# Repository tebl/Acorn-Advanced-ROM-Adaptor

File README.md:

# Acorn Advanced ROM Adaptor

Recently picked up something called an Advanced ROM MKII Adaptor, a 16K sideways ROM- RAM Adaptor for The Acorn Electron by Advanced Computer Products. The one I have looks like the one below, unfortunately it was had no sockets so both all the ROMs were soldered in and the jumpers used to select the type of chips installed (8K SRAM, 8K ROM or 16K ROM) were nowhere to be seen so not the most exciting piece of kit in my collection. So I decided to recreate the board instead of tearing it down and hacking it to pieces.

The original release of the product had a MKI which only sported a single EPROM, the MKII as already described has the capacity for two chips with the aid of a small piece of added logic. I started by tracing out where every connection went on the MKII, adding up the details into a [schematic](https://github.com/tebl/Acorn-Advanced-ROM-Adaptor/raw/master/MK2%20Original/export/MK2%20Original.pdf) that can be found as part of the project found in*MK2 Original*. I've included them for any that would like to have that kind of information available when attempting to repair a similar cartridge.

Finally I wanted one that I could mess around with, so with the schematic in mind I started drawing out a *MKIII Redux* version of it instead. The differences here is that I've replaced the 27128/27C128, that are a pain to track down and pay for, with the plentiful 27C512 chips instead. This bumps the capacity of the cartridge from 2x16K to 8x16K, addressing is kept the same - the remaining slots are available by changing the jumper settings. 

# Versions
For added details, see following project pages:
- [MKII Original](https://github.com/tebl/Acorn-Advanced-ROM-Adaptor/tree/master/MK2%20Original)
- [MKIII Redux](https://github.com/tebl/Acorn-Advanced-ROM-Adaptor/tree/master/MK3%20Redux)

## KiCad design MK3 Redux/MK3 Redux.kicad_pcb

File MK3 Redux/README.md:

# Acorn Advanced ROM MKIII Redux

**UNTESTED**

Recently picked up something called an Advanced ROM MKII Adaptor, a 16K sideways ROM- RAM Adaptor for The Acorn Electron by Advanced Computer Products.  I've added a schematic for the MKII as part as the [MKII Original](https://github.com/tebl/Acorn-Advanced-ROM-Adaptor/tree/master/MK2%20Original), this is the *MKIII Redux* and as the name implies it is my attempt to create a cartridge that I can mess around with - without tearing down and hacking up 30 year old irreplaceable hardware.

The differences from the original design is that I've replaced the 27128/27C128, that are a pain to track down and pay for, with the plentiful 27C512. This bumps the capacity of the cartridge from 2x16K to 8x16K though addressing is kept the same, the remaining slots are available by changing the jumper settings with the computer is unplugged. I could have gone for chips that are even larger in capacity, but I wanted something that is easy enough for anyone with a soldering iron to fix up for themselves and there really aren't all that much ROM-based software available so even with the limited 8 slots you'll still fit in most of the desirable titles anyway. Smaller EPROMs such as the 27C64 or 27C256 can still be used, just keep the A14/15 lines unjumpered.

# Schematic
The supplied KiCad files should be sufficient as both a schematic and as a  starting point for ordering PCBs (basically you could just zip the contents of the export folder and upload that on a fabrication site), the schematic is also available in [PDF-format](https://github.com/tebl/Acorn-Advanced-ROM-Adaptor/raw/master/MK3%20Redux/export/MK3%20Redux.pdf) and this is what you'll need to print and work your way through this things don't work as expected after assembly.

# BOM
Most parts should be easy to get a hold of from your favourite local electronic component shop, but given that I don't have access to such shops where I live so everything was based on whatever I could get cheapest from ebay/AliExpress (free shipping, plan on usually waiting 3-4 weeks though). The list below should be everything you'll need in addition to a workable soldering iron and some 60/40 soldering tin. Other tools needed for this project is an EPROM-ereaser as well as an EPROM-programmer for the two ICs (I use MiniPro TL866 for both).

Some vendors will have the same ICs in different form factors, the ones you want will often be specified as being in the form of a DIP/PDIP package. Usually you'll want sockets for each of the ICs as well, a bag of assorted sockets should be easily available without setting you back more than a couple bucks. With the sockets in place, you don't need to dread having to remove an IC later, this leads to easier fault finding and you can even "borrow" them for other projects later! For the pin headers, you probably won't find the exact pin count so just buy the longer versions and snip off the parts you don't need.

| Reference    | Item                                  | Count |
| ------------ | ------------------------------------- | ----- |
| PCB          | Fabricate using Gerber files          |     1 |
| C1-C3        | 100nF ceramic capacitor               |     3 |
| R1           | 10k ohm resistor                      |     1 |
| U1,U2        | 27C512 DIP-28                         |     2 |
| U3           | 74HCT00 DIP-16                        |     1 |
|              | Male 2x40-pin header (break to size)  |     1 |

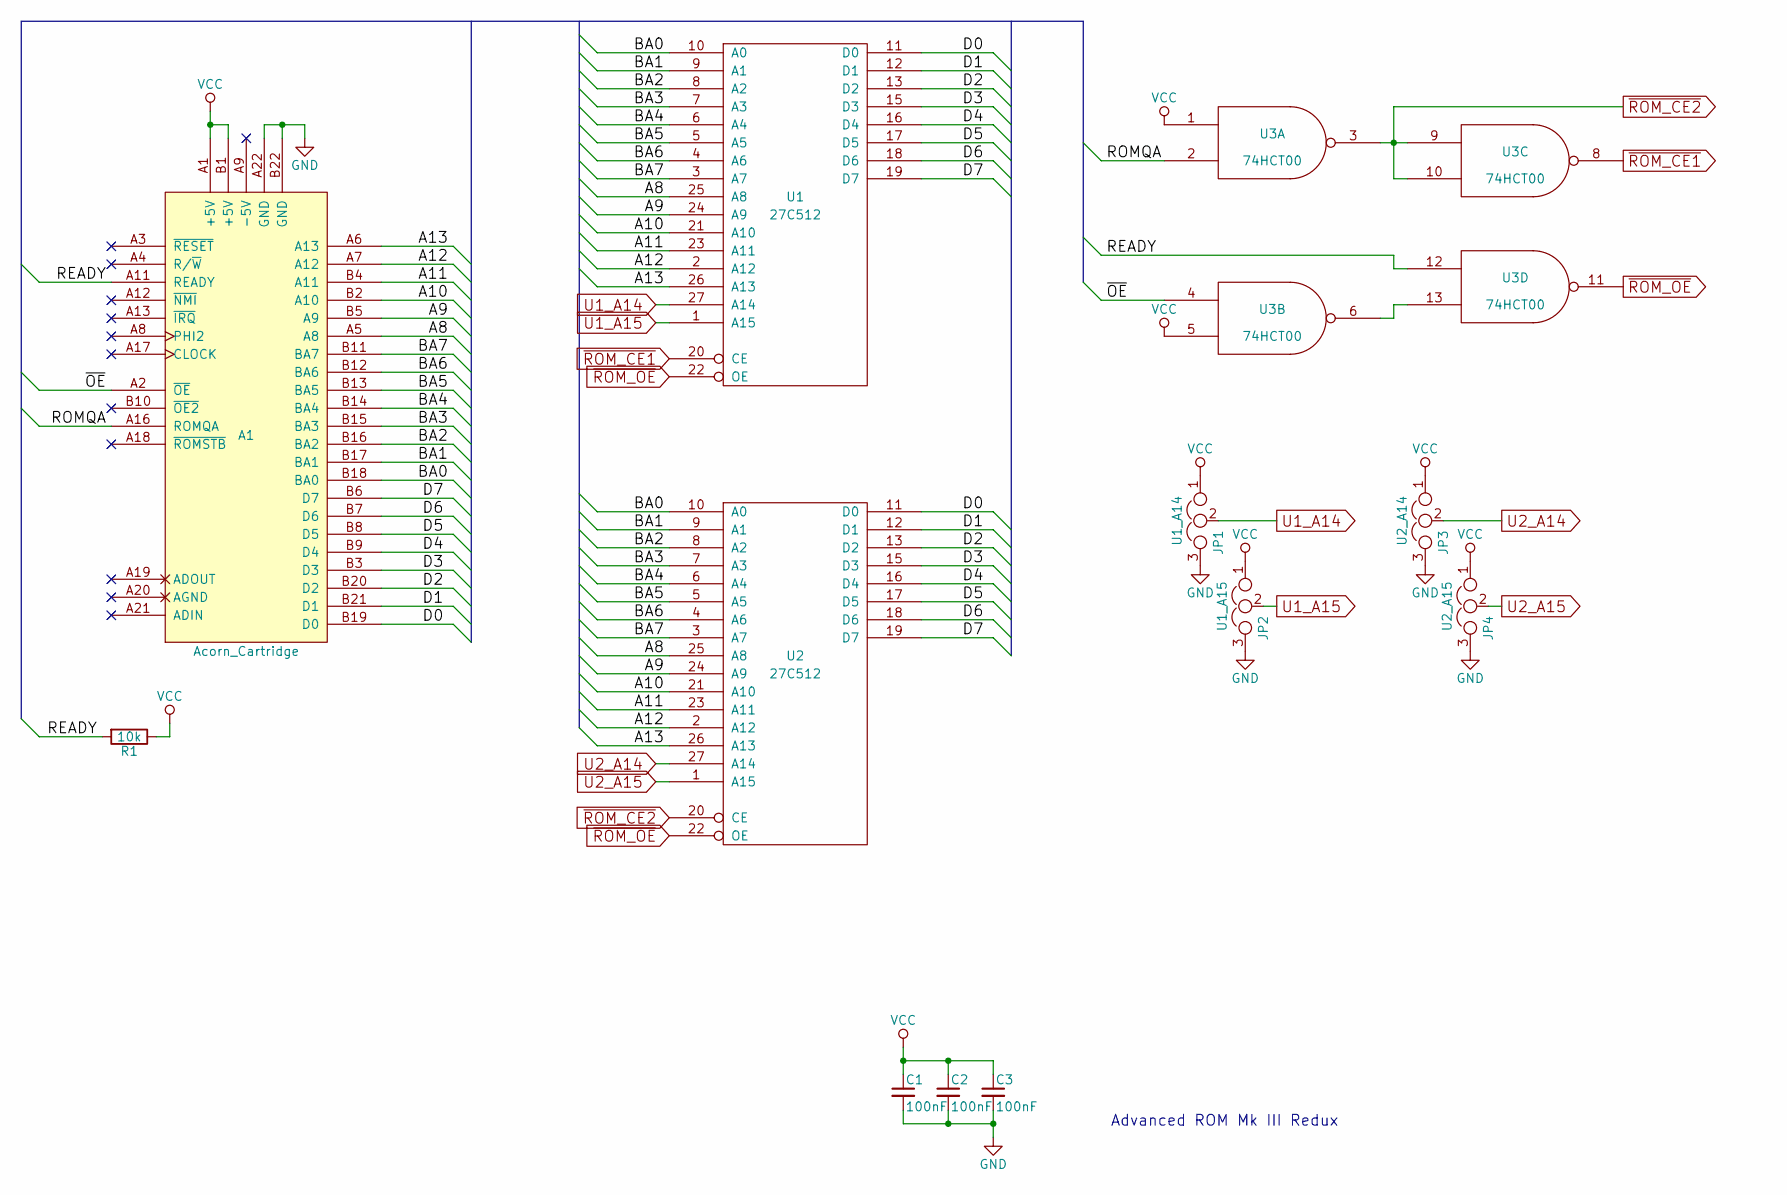
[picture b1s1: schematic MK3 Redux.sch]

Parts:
A1: Acorn_Cartridge
C1, C2, C3: 100nF; C_Disc_D4.7mm_W2.5mm_P5.00mm
JP1: U1_A14; Pin_Header_Straight_1x03_Pitch2.54mm
JP2: U1_A15; Pin_Header_Straight_1x03_Pitch2.54mm
JP3: U2_A14; Pin_Header_Straight_1x03_Pitch2.54mm
JP4: U2_A15; Pin_Header_Straight_1x03_Pitch2.54mm
R1: 10k; R_Axial_DIN0207_L6.3mm_D2.5mm_P10.16mm_Horizontal
U1, U2: 27C512; DIP-28_W15.24mm_Socket
U3: 74HCT00; DIP-14_W7.62mm_Socket

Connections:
/A8: A1.A5 (A8), U1.25 (A8), U2.25 (A8)
/A9: A1.B5 (A9), U1.24 (A9), U2.24 (A9)
/A10: A1.B2 (A10), U1.21 (A10), U2.21 (A10)
/A11: A1.B4 (A11), U1.23 (A11), U2.23 (A11)
/A12: A1.A7 (A12), U1.2 (A12), U2.2 (A12)
/A13: A1.A6 (A13), U1.26 (A13), U2.26 (A13)
/BA0: A1.B18 (BA0), U1.10 (A0), U2.10 (A0)
/BA1: A1.B17 (BA1), U1.9 (A1), U2.9 (A1)
/BA2: A1.B16 (BA2), U1.8 (A2), U2.8 (A2)
/BA3: A1.B15 (BA3), U1.7 (A3), U2.7 (A3)
/BA4: A1.B14 (BA4), U1.6 (A4), U2.6 (A4)
/BA5: A1.B13 (BA5), U1.5 (A5), U2.5 (A5)
/BA6: A1.B12 (BA6), U1.4 (A6), U2.4 (A6)
/BA7: A1.B11 (BA7), U1.3 (A7), U2.3 (A7)
/D0: A1.B19 (D0), U1.11 (D0), U2.11 (D0)
/D1: A1.B21 (D1), U1.12 (D1), U2.12 (D1)
/D2: A1.B20 (D2), U1.13 (D2), U2.13 (D2)
/D3: A1.B3 (D3), U1.15 (D3), U2.15 (D3)
/D4: A1.B9 (D4), U1.16 (D4), U2.16 (D4)
/D5: A1.B8 (D5), U1.17 (D5), U2.17 (D5)
/D6: A1.B7 (D6), U1.18 (D6), U2.18 (D6)
/D7: A1.B6 (D7), U1.19 (D7), U2.19 (D7)
/READY: A1.A11 (READY), R1.2, U3.12
/ROMQA: A1.A16 (ROMQA), U3.2
/~OE: A1.A2 (~OE), U3.4
GND: A1.A22 (GND), A1.B22 (GND), C1.2, C2.2, C3.2, JP1.3, JP2.3, JP3.3, JP4.3, U1.14 (GND), U2.14 (GND), U3.7 (GND)
unnamed: U3.6, U3.13
U1_A14: JP1.2, U1.27 (A14)
U1_A15: JP2.2, U1.1 (A15)
U2_A14: JP3.2, U2.27 (A14)
U2_A15: JP4.2, U2.1 (A15)
VCC: A1.A1 (+5V), A1.B1 (+5V), C1.1, C2.1, C3.1, JP1.1, JP2.1, JP3.1, JP4.1, R1.1, U1.28 (VCC), U2.28 (VCC), U3.1, U3.5, U3.14 (VCC)
~ROM_CE1: U1.20 (CE), U3.8
~ROM_CE2: U2.20 (CE), U3.3, U3.9, U3.10
~ROM_OE: U1.22 (OE), U2.22 (OE), U3.11

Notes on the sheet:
Advanced ROM Mk III Redux

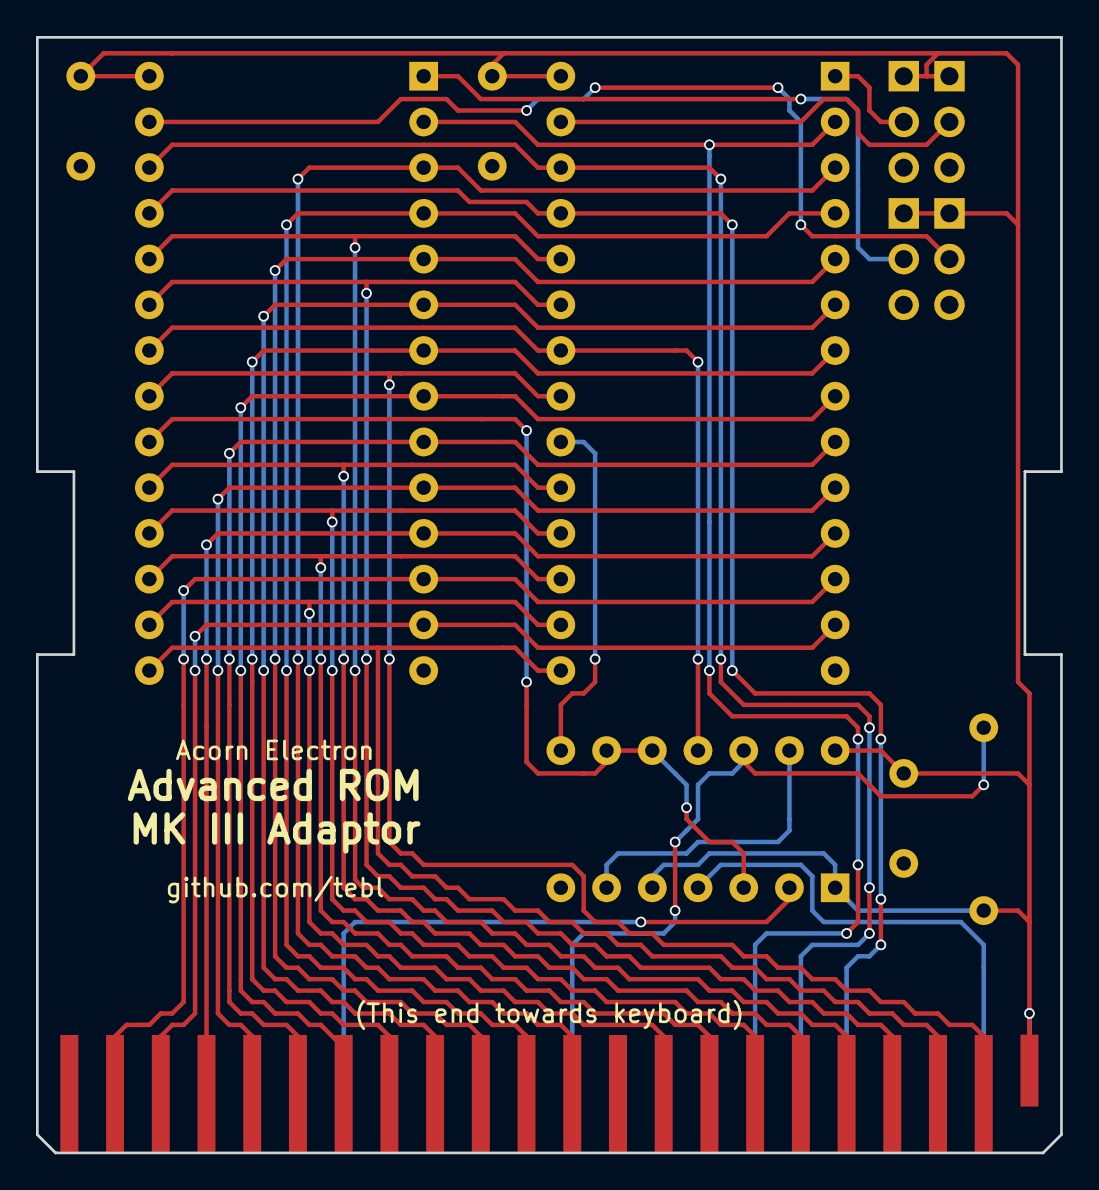
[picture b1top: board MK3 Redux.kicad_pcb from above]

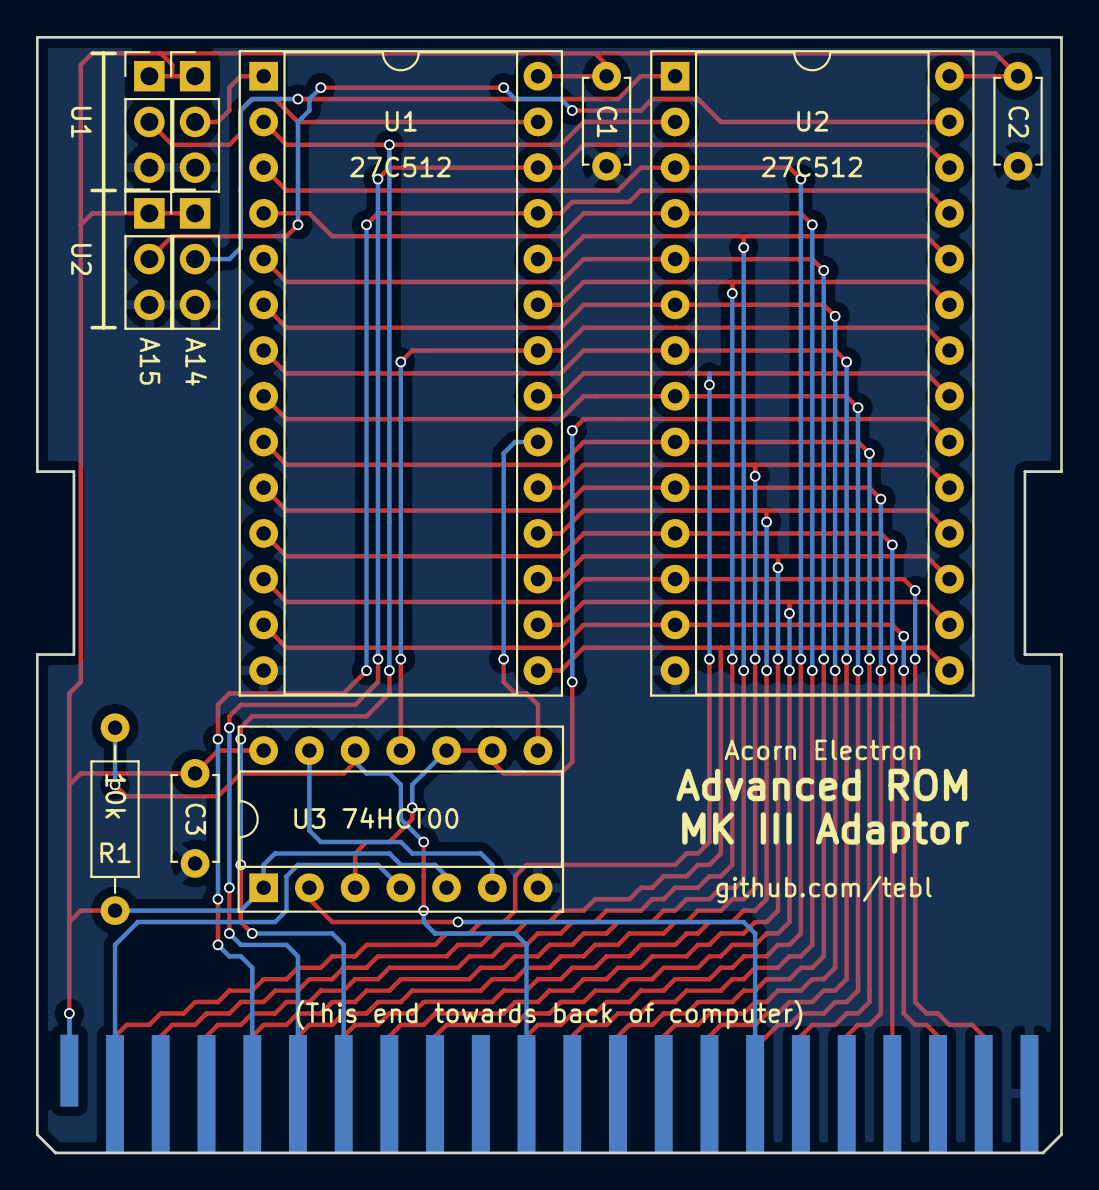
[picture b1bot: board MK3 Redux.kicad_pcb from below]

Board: 2 copper layers, 56.9 x 62.0 mm, 12 parts (11 on the bottom side), 35 nets.

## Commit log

2019-09-12 MK2 schematic recreated
2019-09-12 Created MK3 Redux board
2019-09-13 Added schematic pdf
2019-09-13 Added main README
2019-09-13 Added MKII/MKIII README
2019-09-13 Added preview
2019-09-13 Gerber export
